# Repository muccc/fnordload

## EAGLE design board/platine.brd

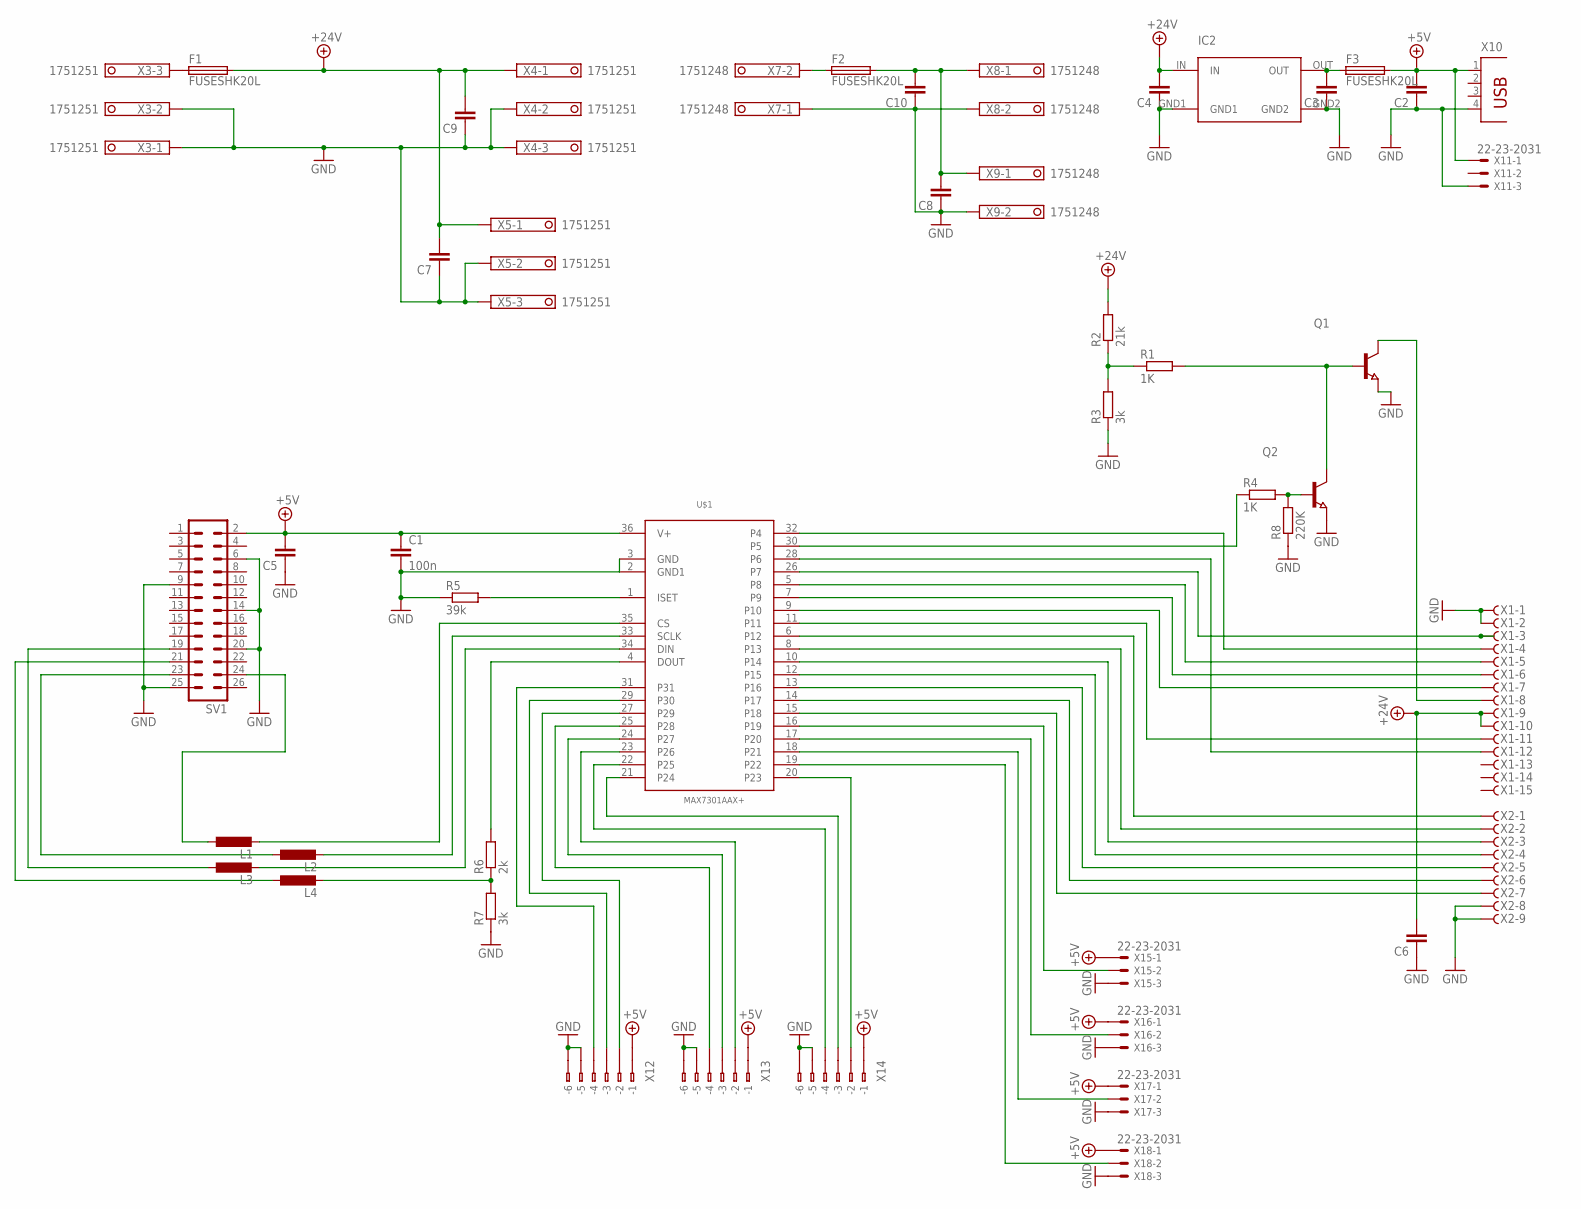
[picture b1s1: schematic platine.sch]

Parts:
C1: 100n; C0603
C2, C3, C4, C5, C6, C7, C8, C9, C10: C-EUC1206; C1206
F1, F2, F3: FUSESHK20L; SHK20L
IC2: SPS-1
L1, L2, L3, L4: L-EUL0402; R0402
Q1, Q2: NPN-TRANSISTOR_SOT23; SOT23
R1, R4: 1K; R0603
R2: 21k; R0603
R3, R7: 3k; R0603
R5: 39k; R0603
R6: 2k; R0603
R8: 220K; R0603
SV1: MA13-2
U$1: MAX7301AAX+; SSOP36
X1: F15HPS; F15HP
X2: F09HPS; F09HP
X3, X4, X5: 1751251
X7, X8, X9: 1751248
X10: PN87520
X11, X15, X16, X17, X18: 22-23-2031
X12, X13, X14: 233-506

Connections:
+5V: C1.1, C2.2, C5.2, F3.2A (2), SV1.2, U$1.36 (V+), X10.1, X11.1, X12.B1 (B-1), X13.B1 (B-1), X14.B1 (B-1), X15.1, X16.1, X17.1, X18.1
+24V: C4.2, C6.2, C7.2, C9.2, F1.2A (2), IC2.IN, R2.2, X1.9, X1.10, X4.1, X5.1
GND: C1.2, C2.1, C3.1, C4.1, C5.1, C6.1, C7.1, C8.1, C9.1, C10.1, IC2.GND1, IC2.GND2, Q1.2 (E), Q2.2 (E), R3.1, R5.1, R7.1, R8.1, SV1.6, SV1.9, SV1.14, SV1.20, SV1.25, U$1.2 (GND1), U$1.3 (GND), X1.1, X1.2, X2.8, X2.9, X3.1, X3.2, X4.2, X4.3, X5.2, X5.3, X7.1, X8.2, X9.2, X10.4, X11.3, X12.B5 (B-5), X12.B6 (B-6), X13.B5 (B-5), X13.B6 (B-6), X14.B5 (B-5), X14.B6 (B-6), X15.3, X16.3, X17.3, X18.3
unnamed: R1.1, R2.1, R3.2
unnamed: Q1.1 (B), Q2.3 (C), R1.2
unnamed: Q2.1 (B), R4.2, R8.2
unnamed: R4.1, U$1.30 (P5)
unnamed: L1.2, U$1.35 (CS)
unnamed: L4.1, SV1.21
unnamed: Q1.3 (C), X1.8
unnamed: U$1.32 (P4), X1.4
unnamed: U$1.28 (P6), X1.12
unnamed: U$1.26 (P7), X1.3
unnamed: U$1.5 (P8), X1.5
unnamed: U$1.7 (P9), X1.6
unnamed: U$1.9 (P10), X1.7
unnamed: U$1.11, X1.11
unnamed: U$1.6 (P12), X2.1
unnamed: U$1.8 (P13), X2.2
unnamed: U$1.10 (P14), X2.3
unnamed: U$1.12 (P15), X2.4
unnamed: U$1.13 (P16), X2.5
unnamed: U$1.14 (P17), X2.6
unnamed: U$1.15 (P18), X2.7
unnamed: L2.2, U$1.33 (SCLK)
unnamed: L3.2, U$1.34 (DIN)
unnamed: R6.2, U$1.4 (DOUT)
unnamed: U$1.16 (P19), X15.2
unnamed: R5.2, U$1.1 (ISET)
unnamed: U$1.17 (P20), X16.2
unnamed: U$1.18 (P21), X17.2
unnamed: U$1.19 (P22), X18.2
unnamed: U$1.20 (P23), X14.B2 (B-2)
unnamed: U$1.21 (P24), X14.B3 (B-3)
unnamed: U$1.22 (P25), X14.B4 (B-4)
unnamed: U$1.23 (P26), X13.B2 (B-2)
unnamed: U$1.24 (P27), X13.B3 (B-3)
unnamed: U$1.25 (P28), X13.B4 (B-4)
unnamed: U$1.27 (P29), X12.B2 (B-2)
unnamed: U$1.29 (P30), X12.B3 (B-3)
unnamed: U$1.31, X12.B4 (B-4)
unnamed: F1.1A (1), X3.3
unnamed: C3.2, F3.1A (1), IC2.OUT
unnamed: L1.1, SV1.24
unnamed: F2.1A (1), X7.2
unnamed: C8.2, C10.2, F2.2A (2), X8.1, X9.1
unnamed: L2.1, SV1.23
unnamed: L3.1, SV1.19
unnamed: L4.2, R6.1, R7.2

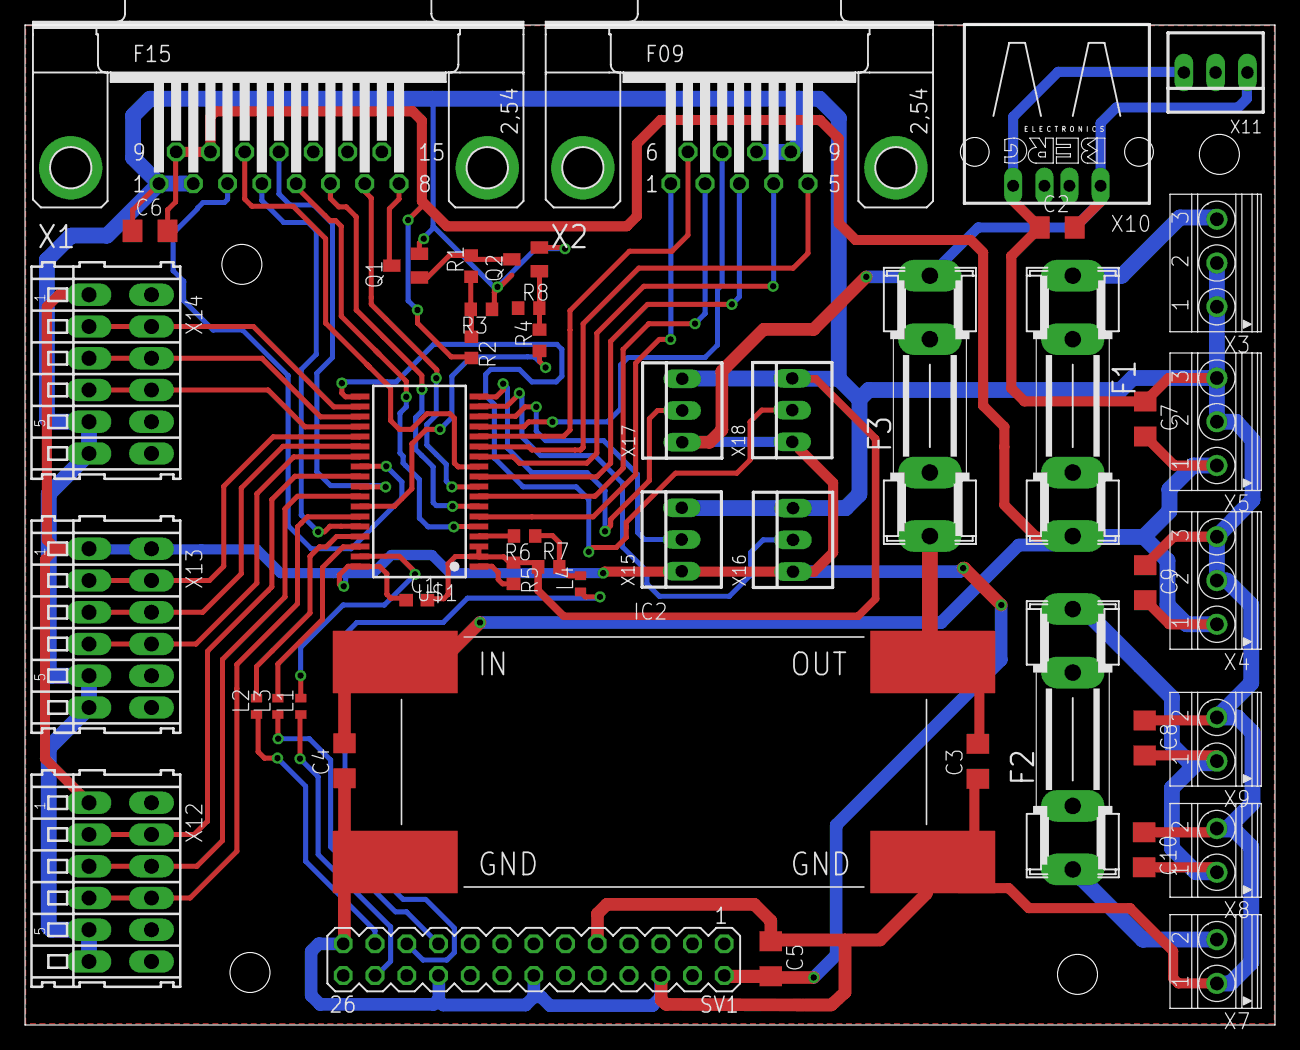
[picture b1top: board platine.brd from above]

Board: 2 copper layers, 100.0 x 80.0 mm, 47 parts (0 on the bottom side), 49 nets.

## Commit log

2013-06-22 Adding eSSP as submodule
2013-06-22 dd Maxim 7301 IO Expander
2013-06-22 added latest schematic
2013-06-22 Ignore Eagle stuff
2013-06-23 added dc/dc converter
2013-06-23 added a suggestion for the placement
2013-06-23 Initial (pretty dirty code) for fnordload
2013-06-23 added quick2wire submodule
2013-09-16 New board
2013-09-22 fix(board): switch MISO and MOSI
2013-09-22 feat(max7301): add suppor files for max7301
2013-09-22 doc(max7301): readme and spi-setup script update
2013-09-25 Replaced wrong transistor
2013-10-02 added py-spidev submodule
2013-10-02 feat(max7301): create a python library for max7301
2013-10-02 Using new library for payout
2013-10-02 New script to empty cashbox
2013-10-02 Removing quick2wire submodule
2013-10-03 Added reset-functionality on quit
2013-12-15 fix(fnordload): sync the fielsystem before giving out coins
2013-12-15 fix(fnordload): add hash bang to script
2013-12-15 chore(fnordload): rename fnordload.py to fnordload
2014-01-11 Some minor changes in production environment
2014-01-11 eSSP updated
2014-04-06 feat(keypad): keypad demo
2014-04-10 fix(spi-setup): use sed inplace
2014-04-10 chore(mx7301): remove the py-max7301 directory. It is on pypi now
2014-04-11 feat(cad): added cad files for the mounting plate
2014-04-11 feat(board): laser layer with outline and holes
2014-04-11 chore(fnordload): move stuff into a module and scripts folder
2014-04-11 feat(setup.py): add a setup.py and scripts folder
2014-04-14 feat(note_validator): first shot at a note validator class
2014-04-14 feat(coin_hopper): sceleton for a coin hopper class
2014-04-14 fix(note-validator): add missing poll handling
2014-04-14 fix(note-validator): add NoteValidator to the module
2014-04-14 refact(fnordload): first shot at using the NoteValidator class
2014-04-14 fix(fnordload): bux fixes
2014-04-22 fix(fnordload): remove unneeded essp import from script
2014-04-22 refact(fnordload): factor out coin hopper into its own class
2014-04-22 fix(fnordload): add missing CoinHopper import to __init__.py
2014-04-22 fix(CoinHopper): add missing import
2014-04-22 fix(CoinHooper): remove get_ from properties
2014-04-22 fix(CoinHooper): remove usage of double under
2014-04-22 fix(CoinHooper): add missing time import
2014-04-22 fix(fnordload): use the reset() method of the coin hopper
2014-04-22 chore(fnordload): remove unneeded max7301 import
2014-04-22 chore(fnordload): remove double unders
2014-04-26 fix(NoteValidator): use proper locking of the eSSP interface
2014-04-26 fix(fnordload): make sure the process exits
2014-04-26 feat(KeyPad): function to wait for and read a single key
2014-04-26 feat(UI): first shot at an UI class
2014-04-27 fix(keypad): 30 s default timeout for get_single_key
2014-04-27 fix(ui): accept an lcd as parameter to the constructor
2014-04-27 fix(lcd): show numbers before the options
2014-04-27 fix(lcd): working example
2014-04-27 fix(NoteValidator): do not block the thread if the queue is full
2014-04-27 fix(Keypad): use fnordload.TimeoutError
2014-04-27 fix(UI): return the original option value
2014-04-27 fix(UI): add the UI class to the package
2014-04-27 feat(fnordload): new menu system
2014-04-27 feat(fnordload): first nupay integration
2014-04-29 feat(coin_hopper): function to increase the coin level
2014-04-29 refact(UI): get the keypad from the constructor
2014-04-29 feat(fnordload): show upay balance and load coins
2014-05-01 refact(ui): let UI.choose accept a complex menu
2014-05-01 feat(fnordload): use the * as back key
2014-05-01 refact(ui): function to input a number
2014-05-01 feat(fnordload): menu option to get coins
2014-05-01 chore(fnordload-empty): remove unused script
2014-05-01 fix(NoteValidator): dsable the validator if an error occours
2014-05-01 fix(LCD): do not start flashing the LCD
2014-05-01 feat(fnordload): write new tokens to usb drives
2014-05-10 chore(eSSP): use new version of submodule
2014-05-10 refact(utils): move sync function to a utils class
2014-05-10 feat(fnordload): use a command line argument as management code
2014-05-10 refact(CoinHopper): new Account class to store the coin level
2014-05-11 fix(CoinHopper): use correct method name of the account
2014-05-11 feat(NoteHandler): new class to handle accounts for the note validator
2014-05-11 feat(fnordload): use the NoteHandler class
2014-05-11 chore(fnordload): add empty local-purse file
2014-05-18 fix(NoteValidator): use initial inhibt as constant mask
2014-05-18 feat(keypad): add accepted_keys parameter to get_single_key
2014-05-18 feat(NoteHandler): always check if the account has been loaded
2014-05-18 feat(fnordload): add statistics menu
2014-05-18 feat(fnordload): new mgt menu layout
2014-05-18 feat(fnordload): menu options for the note validator
2014-05-20 refact(fnordload, ui): more felxible ui subsystem
2014-06-10 feat(logging): add experimental logging.ini
2014-06-15 feat(logging): use a config file to configure logging
2014-06-15 feat(logging): more extensive logging
2014-06-15 fix(logging): add some missing imports, throttle eSSP and mx7301
2014-10-18 fix(ui): Add thinking screen
2014-10-18 fix(note_validator): Less verbose logging
2014-10-18 fix(ui): add default 30s timeout for ui
2014-10-18 feat(ui): Show version in main screen
2014-10-18 fix(setup): make eSSP an external package
2014-10-18 fix(note_validator): Correctly import eSSP
2014-11-29 refactor(upay): change from nupay to upay
2014-11-30 refactor(upay): use upay.common and upay.client packages
2015-02-02 fix(note_validator): Restart the timeout if there is activity
    Otherwise it might trigger a timeout while a bill is currently
    processed.
    Closes #9
2015-06-08 Fix for #9 + some debugging
2015-07-21 Removing old VKP80 driver
2015-07-21 Adding new VKP80-drivers
2015-10-10 Accept new bills after rejecting.
2015-10-17 Added Openscad file for coin vessel
2016-01-21 Adding auto-restart of change-giver after invalid note
2022-05-18 Add USB-ISO + Kabel Pinout
